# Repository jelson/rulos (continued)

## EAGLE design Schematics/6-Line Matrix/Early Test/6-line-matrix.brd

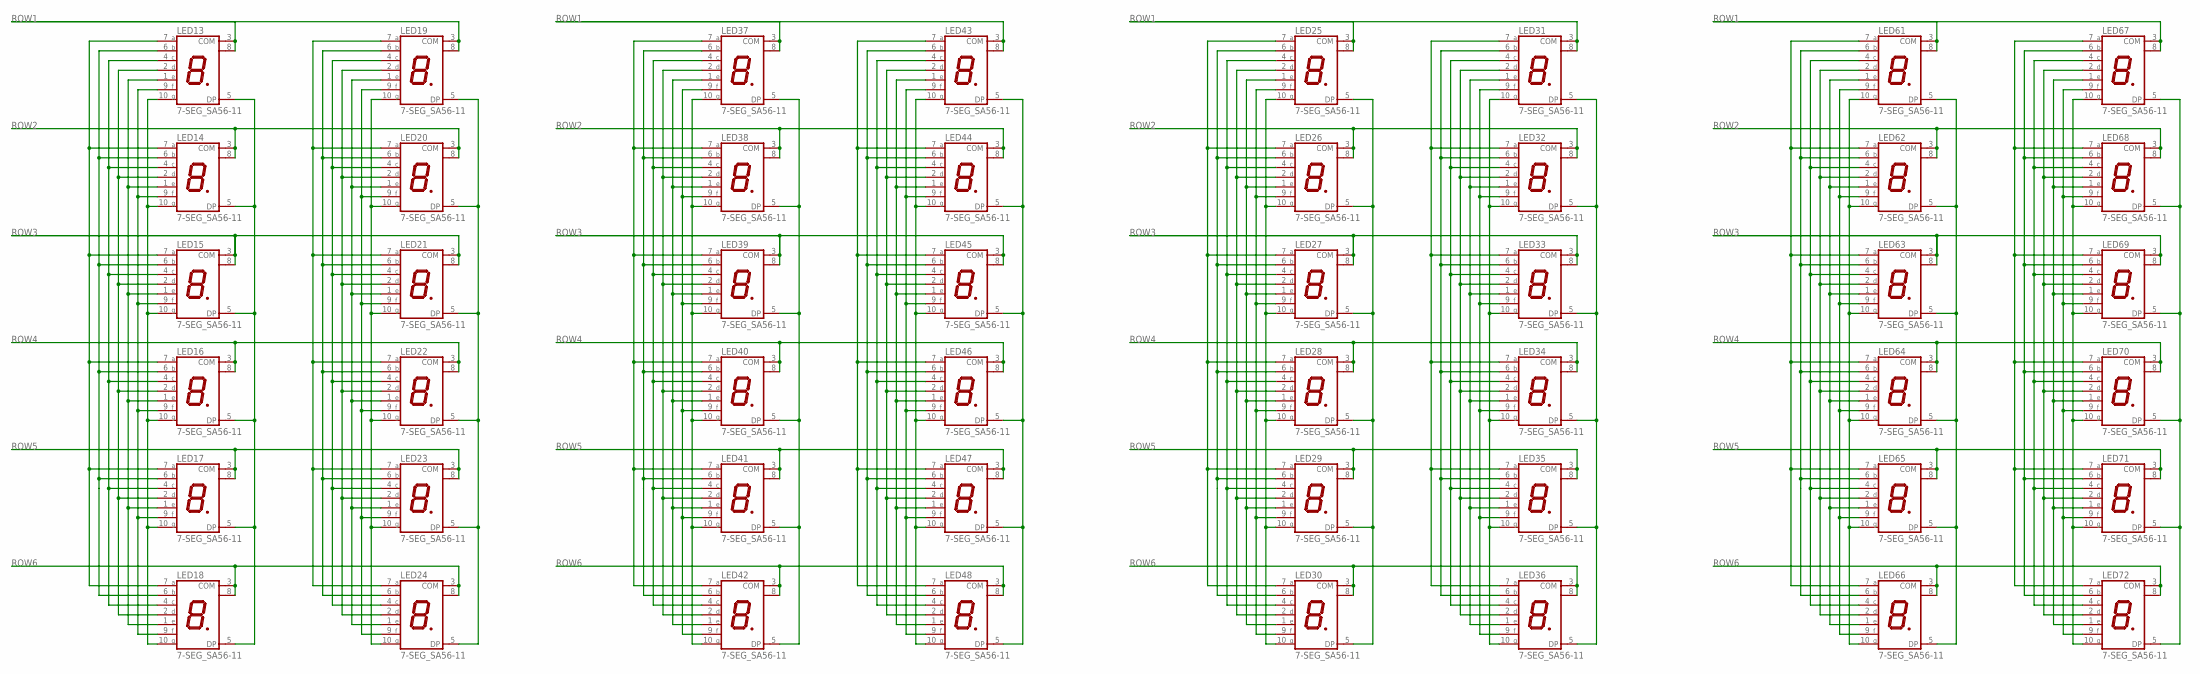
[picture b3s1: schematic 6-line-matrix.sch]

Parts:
LED13, LED14, LED15, LED16, LED17, LED18, LED19, LED20, LED21, LED22, LED23, LED24, LED25, LED26, LED27, LED28, LED29, LED30, LED31, LED32, LED33, LED34, LED35, LED36, LED37, LED38, LED39, LED40, LED41, LED42, LED43, LED44, LED45, LED46, LED47, LED48, LED61, LED62, LED63, LED64, LED65, LED66, LED67, LED68, LED69, LED70, LED71, LED72: 7-SEG_SA56-11; SA56-11

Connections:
unnamed: LED13.7 (A), LED14.7 (A), LED15.7 (A), LED16.7 (A), LED17.7 (A), LED18.7 (A)
unnamed: LED13.6 (B), LED14.6 (B), LED15.6 (B), LED16.6 (B), LED17.6 (B), LED18.6 (B)
unnamed: LED13.10 (G), LED14.10 (G), LED15.10 (G), LED16.10 (G), LED17.10 (G), LED18.10 (G)
unnamed: LED13.9 (F), LED14.9 (F), LED15.9 (F), LED16.9 (F), LED17.9 (F), LED18.9 (F)
unnamed: LED13.1 (E), LED14.1 (E), LED15.1 (E), LED16.1 (E), LED17.1 (E), LED18.1 (E)
unnamed: LED13.2 (D), LED14.2 (D), LED15.2 (D), LED16.2 (D), LED17.2 (D), LED18.2 (D)
unnamed: LED13.4 (C), LED14.4 (C), LED15.4 (C), LED16.4 (C), LED17.4 (C), LED18.4 (C)
unnamed: LED13.5 (DP), LED14.5 (DP), LED15.5 (DP), LED16.5 (DP), LED17.5 (DP), LED18.5 (DP)
unnamed: LED19.10 (G), LED20.10 (G), LED21.10 (G), LED22.10 (G), LED23.10 (G), LED24.10 (G)
unnamed: LED19.9 (F), LED20.9 (F), LED21.9 (F), LED22.9 (F), LED23.9 (F), LED24.9 (F)
unnamed: LED19.1 (E), LED20.1 (E), LED21.1 (E), LED22.1 (E), LED23.1 (E), LED24.1 (E)
unnamed: LED19.2 (D), LED20.2 (D), LED21.2 (D), LED22.2 (D), LED23.2 (D), LED24.2 (D)
unnamed: LED19.4 (C), LED20.4 (C), LED21.4 (C), LED22.4 (C), LED23.4 (C), LED24.4 (C)
unnamed: LED19.6 (B), LED20.6 (B), LED21.6 (B), LED22.6 (B), LED23.6 (B), LED24.6 (B)
unnamed: LED19.7 (A), LED20.7 (A), LED21.7 (A), LED22.7 (A), LED23.7 (A), LED24.7 (A)
unnamed: LED19.5 (DP), LED20.5 (DP), LED21.5 (DP), LED22.5 (DP), LED23.5 (DP), LED24.5 (DP)
unnamed: LED25.7 (A), LED26.7 (A), LED27.7 (A), LED28.7 (A), LED29.7 (A), LED30.7 (A)
unnamed: LED25.6 (B), LED26.6 (B), LED27.6 (B), LED28.6 (B), LED29.6 (B), LED30.6 (B)
unnamed: LED25.10 (G), LED26.10 (G), LED27.10 (G), LED28.10 (G), LED29.10 (G), LED30.10 (G)
unnamed: LED25.9 (F), LED26.9 (F), LED27.9 (F), LED28.9 (F), LED29.9 (F), LED30.9 (F)
unnamed: LED25.1 (E), LED26.1 (E), LED27.1 (E), LED28.1 (E), LED29.1 (E), LED30.1 (E)
unnamed: LED25.2 (D), LED26.2 (D), LED27.2 (D), LED28.2 (D), LED29.2 (D), LED30.2 (D)
unnamed: LED25.4 (C), LED26.4 (C), LED27.4 (C), LED28.4 (C), LED29.4 (C), LED30.4 (C)
unnamed: LED25.5 (DP), LED26.5 (DP), LED27.5 (DP), LED28.5 (DP), LED29.5 (DP), LED30.5 (DP)
unnamed: LED31.10 (G), LED32.10 (G), LED33.10 (G), LED34.10 (G), LED35.10 (G), LED36.10 (G)
unnamed: LED31.9 (F), LED32.9 (F), LED33.9 (F), LED34.9 (F), LED35.9 (F), LED36.9 (F)
unnamed: LED31.1 (E), LED32.1 (E), LED33.1 (E), LED34.1 (E), LED35.1 (E), LED36.1 (E)
unnamed: LED31.2 (D), LED32.2 (D), LED33.2 (D), LED34.2 (D), LED35.2 (D), LED36.2 (D)
unnamed: LED31.4 (C), LED32.4 (C), LED33.4 (C), LED34.4 (C), LED35.4 (C), LED36.4 (C)
unnamed: LED31.6 (B), LED32.6 (B), LED33.6 (B), LED34.6 (B), LED35.6 (B), LED36.6 (B)
unnamed: LED31.7 (A), LED32.7 (A), LED33.7 (A), LED34.7 (A), LED35.7 (A), LED36.7 (A)
unnamed: LED31.5 (DP), LED32.5 (DP), LED33.5 (DP), LED34.5 (DP), LED35.5 (DP), LED36.5 (DP)
unnamed: LED37.7 (A), LED38.7 (A), LED39.7 (A), LED40.7 (A), LED41.7 (A), LED42.7 (A)
unnamed: LED37.6 (B), LED38.6 (B), LED39.6 (B), LED40.6 (B), LED41.6 (B), LED42.6 (B)
unnamed: LED37.10 (G), LED38.10 (G), LED39.10 (G), LED40.10 (G), LED41.10 (G), LED42.10 (G)
unnamed: LED37.9 (F), LED38.9 (F), LED39.9 (F), LED40.9 (F), LED41.9 (F), LED42.9 (F)
unnamed: LED37.1 (E), LED38.1 (E), LED39.1 (E), LED40.1 (E), LED41.1 (E), LED42.1 (E)
unnamed: LED37.2 (D), LED38.2 (D), LED39.2 (D), LED40.2 (D), LED41.2 (D), LED42.2 (D)
unnamed: LED37.4 (C), LED38.4 (C), LED39.4 (C), LED40.4 (C), LED41.4 (C), LED42.4 (C)
unnamed: LED37.5 (DP), LED38.5 (DP), LED39.5 (DP), LED40.5 (DP), LED41.5 (DP), LED42.5 (DP)
unnamed: LED43.10 (G), LED44.10 (G), LED45.10 (G), LED46.10 (G), LED47.10 (G), LED48.10 (G)
unnamed: LED43.9 (F), LED44.9 (F), LED45.9 (F), LED46.9 (F), LED47.9 (F), LED48.9 (F)
unnamed: LED43.1 (E), LED44.1 (E), LED45.1 (E), LED46.1 (E), LED47.1 (E), LED48.1 (E)
unnamed: LED43.2 (D), LED44.2 (D), LED45.2 (D), LED46.2 (D), LED47.2 (D), LED48.2 (D)
unnamed: LED43.4 (C), LED44.4 (C), LED45.4 (C), LED46.4 (C), LED47.4 (C), LED48.4 (C)
unnamed: LED43.6 (B), LED44.6 (B), LED45.6 (B), LED46.6 (B), LED47.6 (B), LED48.6 (B)
unnamed: LED43.7 (A), LED44.7 (A), LED45.7 (A), LED46.7 (A), LED47.7 (A), LED48.7 (A)
unnamed: LED43.5 (DP), LED44.5 (DP), LED45.5 (DP), LED46.5 (DP), LED47.5 (DP), LED48.5 (DP)
unnamed: LED61.7 (A), LED62.7 (A), LED63.7 (A), LED64.7 (A), LED65.7 (A), LED66.7 (A)
unnamed: LED61.6 (B), LED62.6 (B), LED63.6 (B), LED64.6 (B), LED65.6 (B), LED66.6 (B)
unnamed: LED61.10 (G), LED62.10 (G), LED63.10 (G), LED64.10 (G), LED65.10 (G), LED66.10 (G)
unnamed: LED61.9 (F), LED62.9 (F), LED63.9 (F), LED64.9 (F), LED65.9 (F), LED66.9 (F)
unnamed: LED61.1 (E), LED62.1 (E), LED63.1 (E), LED64.1 (E), LED65.1 (E), LED66.1 (E)
unnamed: LED61.2 (D), LED62.2 (D), LED63.2 (D), LED64.2 (D), LED65.2 (D), LED66.2 (D)
unnamed: LED61.4 (C), LED62.4 (C), LED63.4 (C), LED64.4 (C), LED65.4 (C), LED66.4 (C)
unnamed: LED61.5 (DP), LED62.5 (DP), LED63.5 (DP), LED64.5 (DP), LED65.5 (DP), LED66.5 (DP)
unnamed: LED67.10 (G), LED68.10 (G), LED69.10 (G), LED70.10 (G), LED71.10 (G), LED72.10 (G)
unnamed: LED67.9 (F), LED68.9 (F), LED69.9 (F), LED70.9 (F), LED71.9 (F), LED72.9 (F)
unnamed: LED67.1 (E), LED68.1 (E), LED69.1 (E), LED70.1 (E), LED71.1 (E), LED72.1 (E)
unnamed: LED67.2 (D), LED68.2 (D), LED69.2 (D), LED70.2 (D), LED71.2 (D), LED72.2 (D)
unnamed: LED67.4 (C), LED68.4 (C), LED69.4 (C), LED70.4 (C), LED71.4 (C), LED72.4 (C)
unnamed: LED67.6 (B), LED68.6 (B), LED69.6 (B), LED70.6 (B), LED71.6 (B), LED72.6 (B)
unnamed: LED67.7 (A), LED68.7 (A), LED69.7 (A), LED70.7 (A), LED71.7 (A), LED72.7 (A)
unnamed: LED67.5 (DP), LED68.5 (DP), LED69.5 (DP), LED70.5 (DP), LED71.5 (DP), LED72.5 (DP)
ROW1: LED13.3 (COM), LED13.8 (COM), LED19.3 (COM), LED19.8 (COM), LED25.3 (COM), LED25.8 (COM), LED31.3 (COM), LED31.8 (COM), LED37.3 (COM), LED37.8 (COM), LED43.3 (COM), LED43.8 (COM), LED61.3 (COM), LED61.8 (COM), LED67.3 (COM), LED67.8 (COM)
ROW2: LED14.3 (COM), LED14.8 (COM), LED20.3 (COM), LED20.8 (COM), LED26.3 (COM), LED26.8 (COM), LED32.3 (COM), LED32.8 (COM), LED38.3 (COM), LED38.8 (COM), LED44.3 (COM), LED44.8 (COM), LED62.3 (COM), LED62.8 (COM), LED68.3 (COM), LED68.8 (COM)
ROW3: LED15.3 (COM), LED15.8 (COM), LED21.3 (COM), LED21.8 (COM), LED27.3 (COM), LED27.8 (COM), LED33.3 (COM), LED33.8 (COM), LED39.3 (COM), LED39.8 (COM), LED45.3 (COM), LED45.8 (COM), LED63.3 (COM), LED63.8 (COM), LED69.3 (COM), LED69.8 (COM)
ROW4: LED16.3 (COM), LED16.8 (COM), LED22.3 (COM), LED22.8 (COM), LED28.3 (COM), LED28.8 (COM), LED34.3 (COM), LED34.8 (COM), LED40.3 (COM), LED40.8 (COM), LED46.3 (COM), LED46.8 (COM), LED64.3 (COM), LED64.8 (COM), LED70.3 (COM), LED70.8 (COM)
ROW5: LED17.3 (COM), LED17.8 (COM), LED23.3 (COM), LED23.8 (COM), LED29.3 (COM), LED29.8 (COM), LED35.3 (COM), LED35.8 (COM), LED41.3 (COM), LED41.8 (COM), LED47.3 (COM), LED47.8 (COM), LED65.3 (COM), LED65.8 (COM), LED71.3 (COM), LED71.8 (COM)
ROW6: LED18.3 (COM), LED18.8 (COM), LED24.3 (COM), LED24.8 (COM), LED30.3 (COM), LED30.8 (COM), LED36.3 (COM), LED36.8 (COM), LED42.3 (COM), LED42.8 (COM), LED48.3 (COM), LED48.8 (COM), LED66.3 (COM), LED66.8 (COM), LED72.3 (COM), LED72.8 (COM)

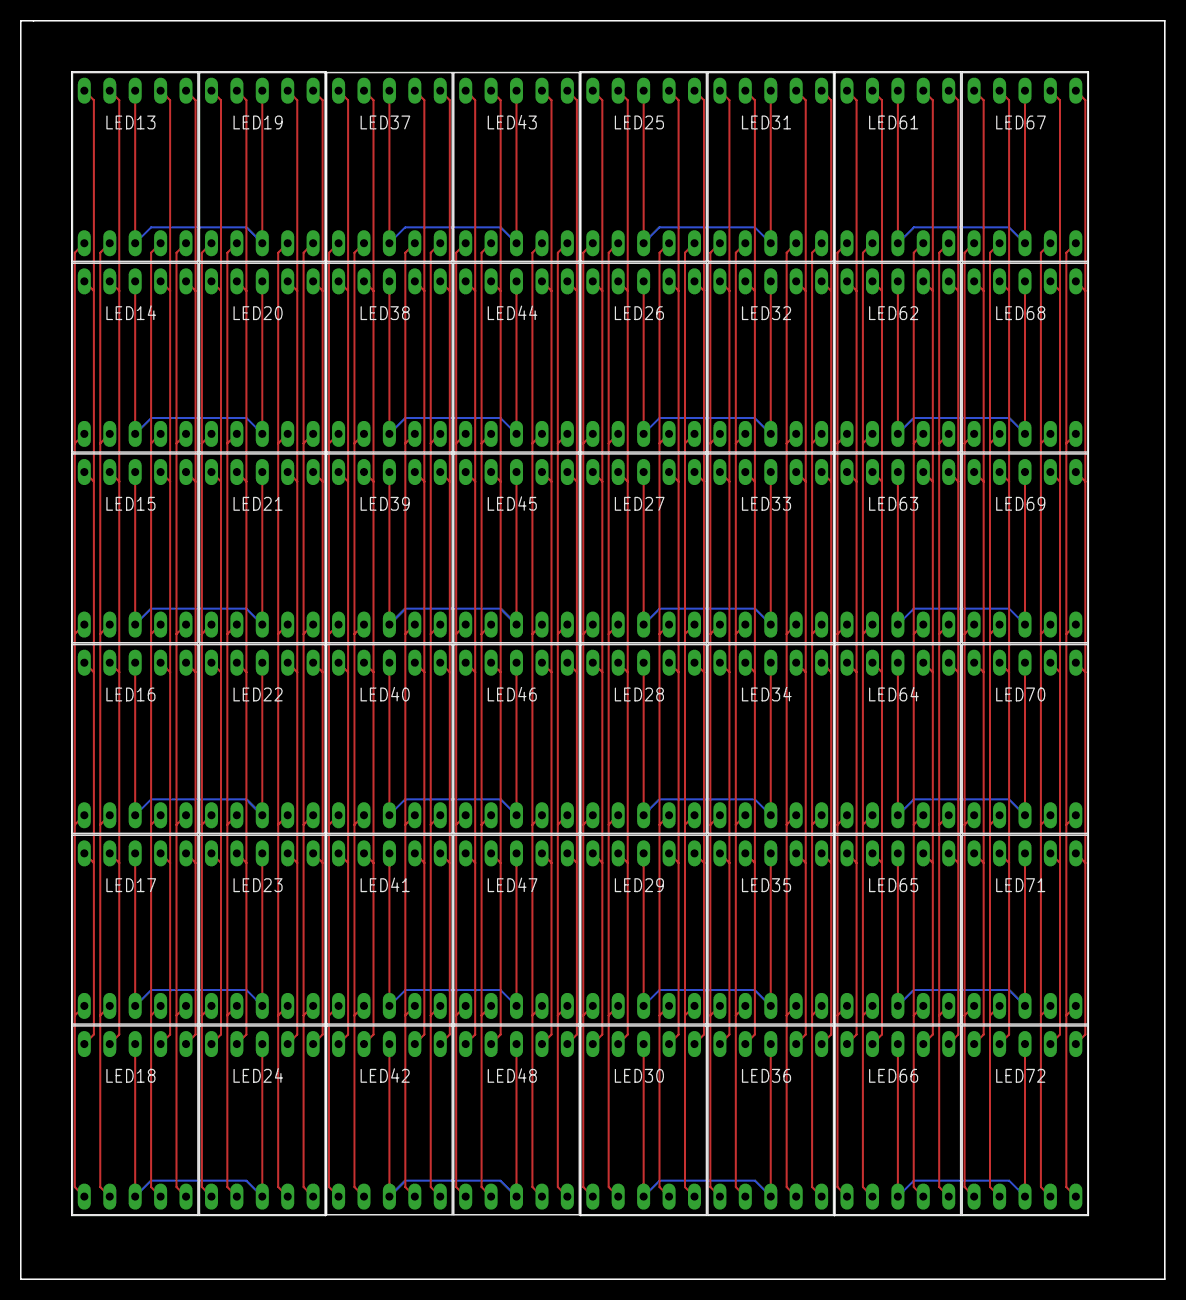
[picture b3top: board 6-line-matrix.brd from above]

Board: 2 copper layers, 114.3 x 125.7 mm, 48 parts (0 on the bottom side), 70 nets.

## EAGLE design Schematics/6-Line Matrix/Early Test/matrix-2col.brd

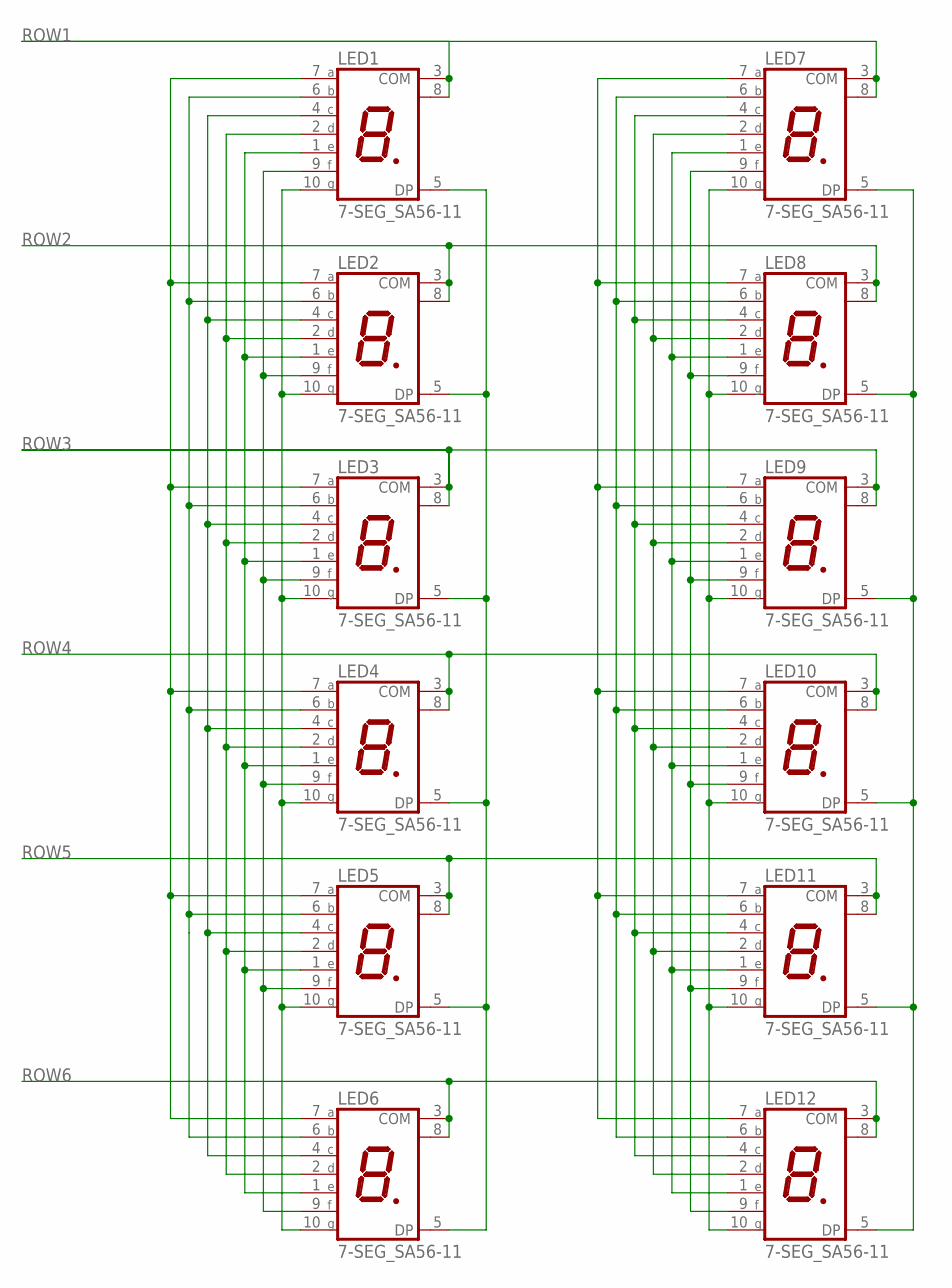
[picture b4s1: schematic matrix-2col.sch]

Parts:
LED1, LED2, LED3, LED4, LED5, LED6, LED7, LED8, LED9, LED10, LED11, LED12: 7-SEG_SA56-11; SA56-11

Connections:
unnamed: LED1.10 (G), LED2.10 (G), LED3.10 (G), LED4.10 (G), LED5.10 (G), LED6.10 (G)
unnamed: LED1.5 (DP), LED2.5 (DP), LED3.5 (DP), LED4.5 (DP), LED5.5 (DP), LED6.5 (DP)
unnamed: LED7.10 (G), LED8.10 (G), LED9.10 (G), LED10.10 (G), LED11.10 (G), LED12.10 (G)
unnamed: LED7.9 (F), LED8.9 (F), LED9.9 (F), LED10.9 (F), LED11.9 (F), LED12.9 (F)
unnamed: LED7.1 (E), LED8.1 (E), LED9.1 (E), LED10.1 (E), LED11.1 (E), LED12.1 (E)
unnamed: LED1.7 (A), LED2.7 (A), LED3.7 (A), LED4.7 (A), LED5.7 (A), LED6.7 (A)
unnamed: LED1.6 (B), LED2.6 (B), LED3.6 (B), LED4.6 (B), LED5.6 (B), LED6.6 (B)
unnamed: LED1.9 (F), LED2.9 (F), LED3.9 (F), LED4.9 (F), LED5.9 (F), LED6.9 (F)
unnamed: LED1.1 (E), LED2.1 (E), LED3.1 (E), LED4.1 (E), LED5.1 (E), LED6.1 (E)
unnamed: LED1.2 (D), LED2.2 (D), LED3.2 (D), LED4.2 (D), LED5.2 (D), LED6.2 (D)
unnamed: LED1.4 (C), LED2.4 (C), LED3.4 (C), LED4.4 (C), LED5.4 (C), LED6.4 (C)
unnamed: LED7.2 (D), LED8.2 (D), LED9.2 (D), LED10.2 (D), LED11.2 (D), LED12.2 (D)
unnamed: LED7.4 (C), LED8.4 (C), LED9.4 (C), LED10.4 (C), LED11.4 (C), LED12.4 (C)
unnamed: LED7.6 (B), LED8.6 (B), LED9.6 (B), LED10.6 (B), LED11.6 (B), LED12.6 (B)
unnamed: LED7.7 (A), LED8.7 (A), LED9.7 (A), LED10.7 (A), LED11.7 (A), LED12.7 (A)
unnamed: LED7.5 (DP), LED8.5 (DP), LED9.5 (DP), LED10.5 (DP), LED11.5 (DP), LED12.5 (DP)
ROW1: LED1.3 (COM), LED1.8 (COM), LED7.3 (COM), LED7.8 (COM)
ROW2: LED2.3 (COM), LED2.8 (COM), LED8.3 (COM), LED8.8 (COM)
ROW3: LED3.3 (COM), LED3.8 (COM), LED9.3 (COM), LED9.8 (COM)
ROW4: LED4.3 (COM), LED4.8 (COM), LED10.3 (COM), LED10.8 (COM)
ROW5: LED5.3 (COM), LED5.8 (COM), LED11.3 (COM), LED11.8 (COM)
ROW6: LED6.3 (COM), LED6.8 (COM), LED12.3 (COM), LED12.8 (COM)

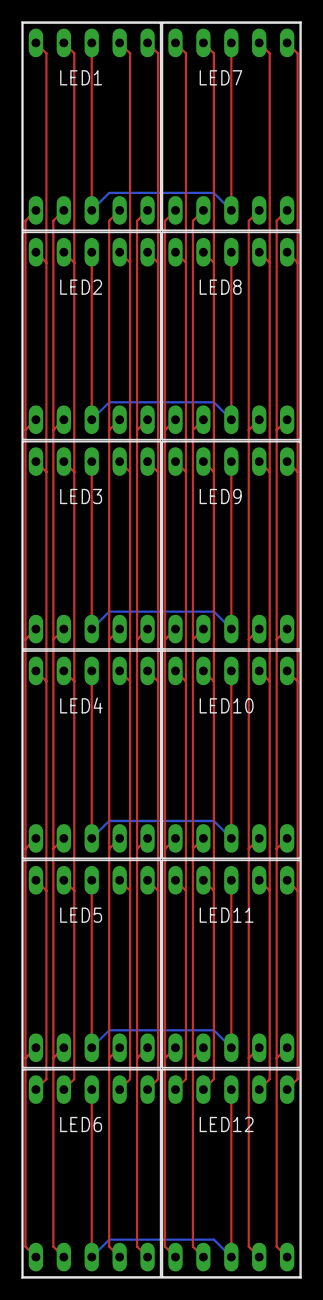
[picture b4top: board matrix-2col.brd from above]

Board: 2 copper layers, 25.4 x 114.3 mm, 12 parts (0 on the bottom side), 22 nets.

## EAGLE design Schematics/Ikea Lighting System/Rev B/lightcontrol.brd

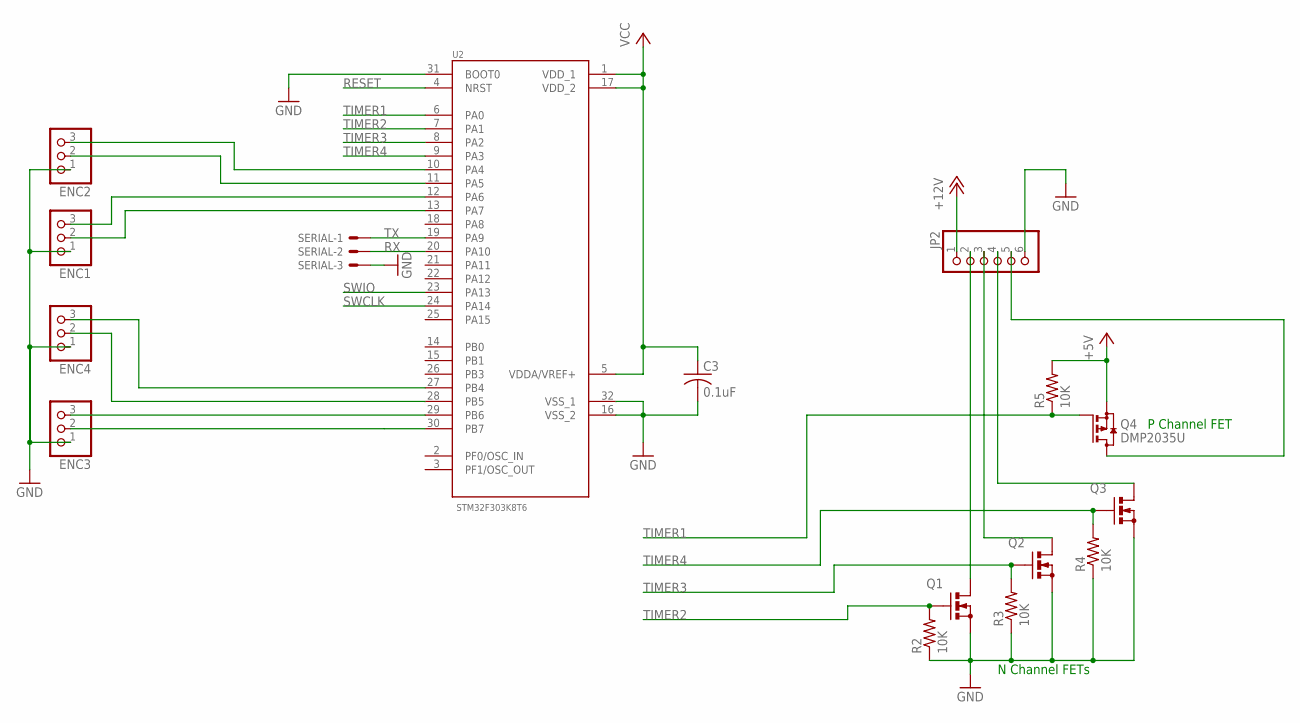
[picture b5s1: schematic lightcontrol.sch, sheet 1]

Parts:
C3: 0.1uF; C0603
ENC1, ENC2, ENC3, ENC4: PINHD-1X3; 1X03
JP2: PINHD-1X6/90; 1X06/90
Q1, Q2, Q3: BS170; SOT54E
Q4: DMP2035U; SOT23
R2, R3, R4, R5: 10K; 0204/5
SERIAL: 22-23-2031
U2: STM32F303K8T6; QFP80P900X900X160-32N

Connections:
+5V: Q4.2 (S), R5.2; also elsewhere on the board
+12V: JP2.1; also elsewhere on the board
GND: C3.2, ENC1.1, ENC2.1, ENC3.1, ENC4.1, JP2.6, Q1.S, Q2.S, Q3.S, R2.1, R3.1, R4.1, SERIAL.3, U2.16 (VSS_2), U2.31 (BOOT0), U2.32 (VSS_1); also elsewhere on the board
unnamed: ENC3.2, U2.30 (PB7)
unnamed: ENC2.3, U2.10 (PA4)
unnamed: ENC3.3, U2.29 (PB6)
unnamed: ENC4.2, U2.28 (PB5)
unnamed: JP2.2, Q1.D
unnamed: ENC2.2, U2.11 (PA5)
unnamed: JP2.3, Q2.D
unnamed: ENC4.3, U2.27 (PB4)
unnamed: JP2.4, Q3.D
unnamed: JP2.5, Q4.3 (D)
unnamed: ENC1.3, U2.12 (PA6)
unnamed: ENC1.2, U2.13 (PA7)
RESET: U2.4 (NRST); also elsewhere on the board
RX: SERIAL.2, U2.20 (PA10)
SWCLK: U2.24 (PA14); also elsewhere on the board
SWIO: U2.23 (PA13); also elsewhere on the board
TIMER1: Q4.1 (G), R5.1, U2.6 (PA0)
TIMER2: Q1.G, R2.2, U2.7 (PA1)
TIMER3: Q2.G, R3.2, U2.8 (PA2)
TIMER4: Q3.G, R4.2, U2.9 (PA3)
TX: SERIAL.1, U2.19 (PA9)
VCC: C3.1, U2.1 (VDD_1), U2.5 (VDDA/VREF+), U2.17 (VDD_2); also elsewhere on the board

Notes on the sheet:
N Channel FETs
P Channel FET

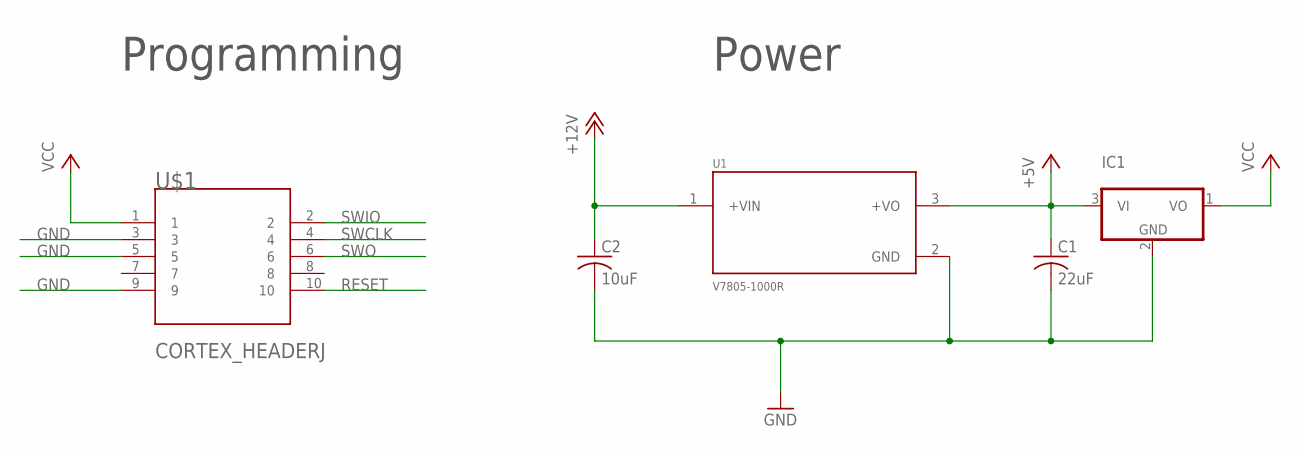
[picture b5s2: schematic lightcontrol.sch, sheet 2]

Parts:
C1: 22uF; C050-035X075
C2: 10uF; C050-035X075
IC1: 7803; TO92
U1: V7805-1000R; CONV_V7805-1000R
U$1: CORTEX_HEADERJ; CORTEX_HEADER

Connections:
+5V: C1.1, IC1.3 (VI), U1.3 (+VO); also elsewhere on the board
+12V: C2.1, U1.1 (+VIN); also elsewhere on the board
GND: C1.2, C2.2, IC1.2 (GND), U1.2 (GND), U$1.3, U$1.5, U$1.9; also elsewhere on the board
RESET: U$1.10; also elsewhere on the board
SWCLK: U$1.4; also elsewhere on the board
SWIO: U$1.2; also elsewhere on the board
SWO: U$1.6
VCC: IC1.1 (VO), U$1.1; also elsewhere on the board

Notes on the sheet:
Programming
Power

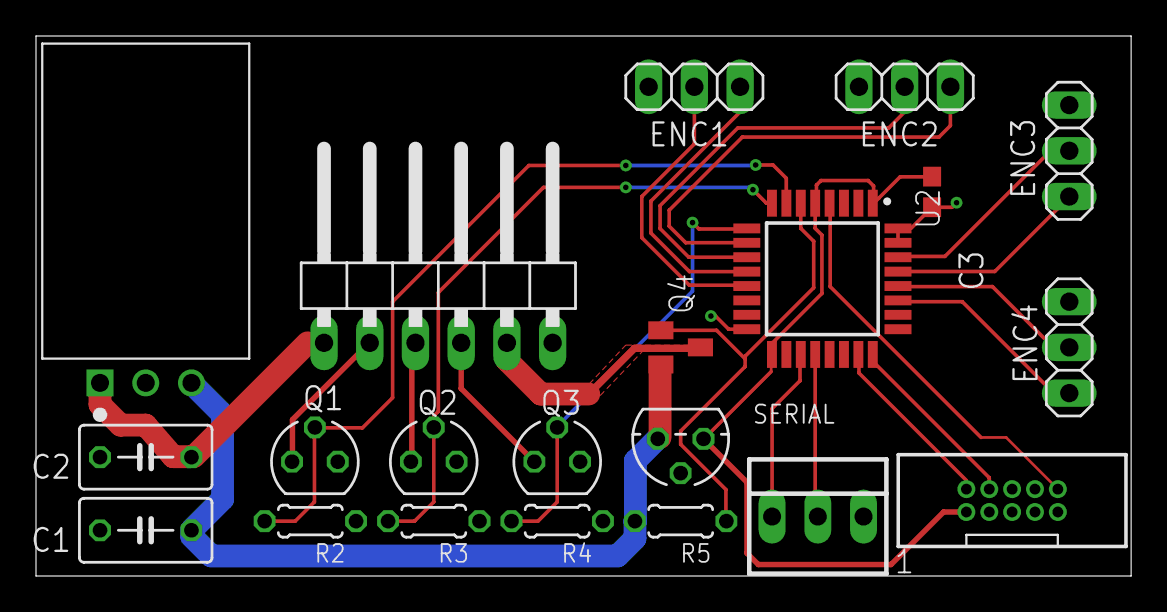
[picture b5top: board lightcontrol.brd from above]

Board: 2 copper layers, 60.8 x 30.0 mm, 21 parts (0 on the bottom side), 25 nets.

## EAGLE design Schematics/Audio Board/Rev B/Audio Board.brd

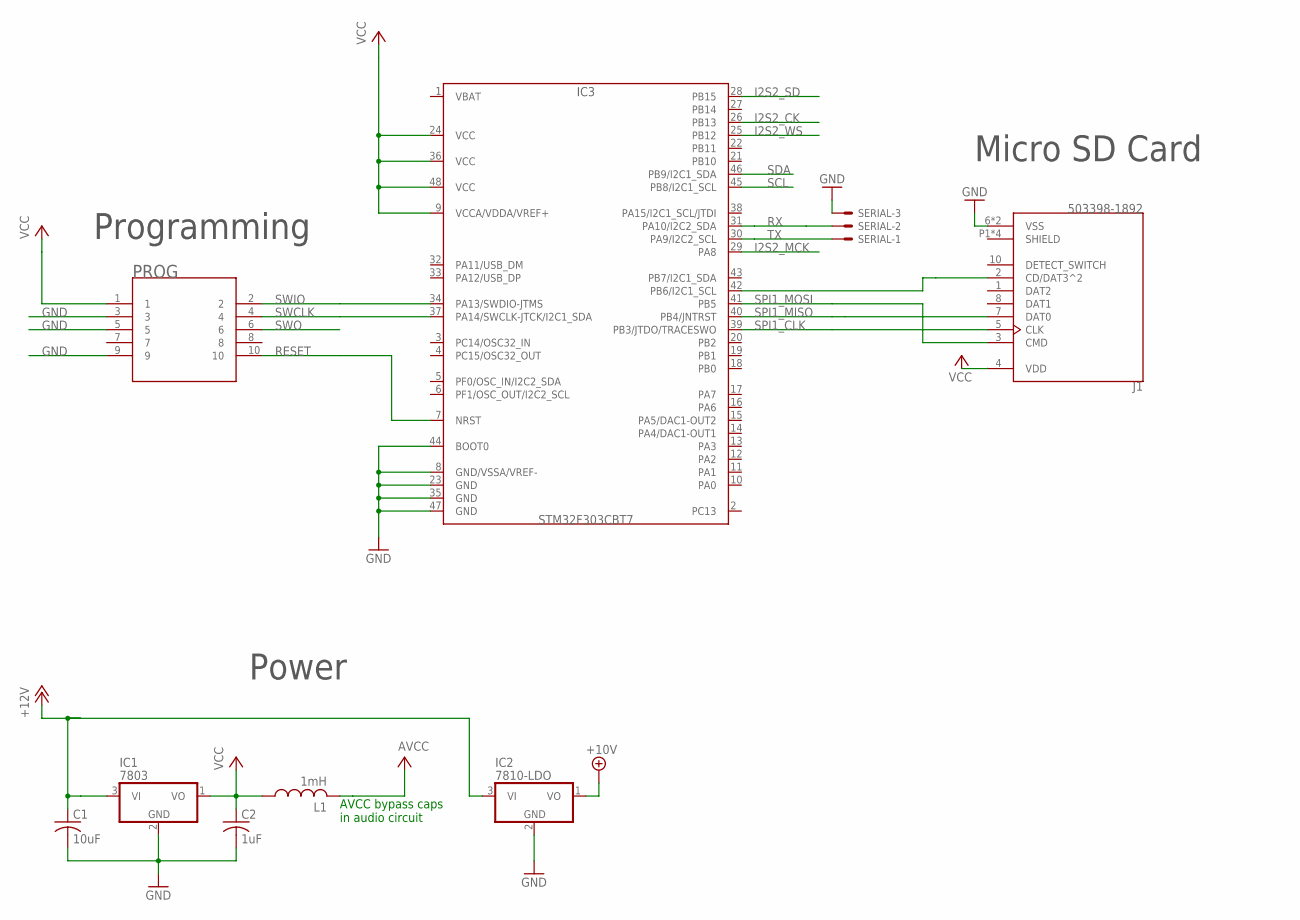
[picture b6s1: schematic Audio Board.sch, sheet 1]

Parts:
C1: 10uF; C025-025X050
C2: 1uF; C025-025X050
IC1: 7803; TO92
IC2: 7810-LDO; TO92
IC3: STM32F303CBT7; LQFP48
J1: 503398-1892; MOLEX_503398-1892
L1: 1mH; 0207/10
PROG: CORTEX_HEADERJ; CORTEX_HEADER
SERIAL: 22-23-2031

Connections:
+10V: IC2.1 (VO); also elsewhere on the board
+12V: C1.1, IC1.3 (VI), IC2.3 (VI); also elsewhere on the board
GND: C1.2, C2.2, IC1.2 (GND), IC2.2 (GND), IC3.8 (GND/VSSA/VREF-), IC3.23 (GND), IC3.35 (GND), IC3.44 (BOOT0), IC3.47 (GND), J1.6 (VSS), J1.9 (VSS), PROG.3, PROG.5, PROG.9, SERIAL.3; also elsewhere on the board
I2S2_CK: IC3.26 (PB13); also elsewhere on the board
I2S2_MCK: IC3.29 (PA8); also elsewhere on the board
I2S2_SD: IC3.28 (PB15); also elsewhere on the board
I2S2_WS: IC3.25 (PB12); also elsewhere on the board
unnamed: IC3.42 (PB6/I2C1_SCL), J1.2 (CD/DAT3^2)
RESET: IC3.7 (NRST), PROG.10
RX: IC3.31 (PA10/I2C2_SDA), SERIAL.2
SCL: IC3.45 (PB8/I2C1_SCL); also elsewhere on the board
SDA: IC3.46 (PB9/I2C1_SDA); also elsewhere on the board
SPI1_CLK: IC3.39 (PB3/JTDO/TRACESWO), J1.5 (CLK)
SPI1_MISO: IC3.40 (PB4/JNTRST), J1.7 (DAT0)
SPI1_MOSI: IC3.41 (PB5), J1.3 (CMD)
SWCLK: IC3.37 (PA14/SWCLK-JTCK/I2C1_SDA), PROG.4
SWIO: IC3.34 (PA13/SWDIO-JTMS), PROG.2
SWO: PROG.6
TX: IC3.30 (PA9/I2C2_SCL), SERIAL.1
V+: L1.2; also elsewhere on the board
VCC: C2.1, IC1.1 (VO), IC3.9 (VCCA/VDDA/VREF+), IC3.24 (VCC), IC3.36 (VCC), IC3.48 (VCC), J1.4 (VDD), L1.1, PROG.1; also elsewhere on the board

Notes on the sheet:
Programming
Power
Micro SD Card
AVCC bypass caps in audio circuit

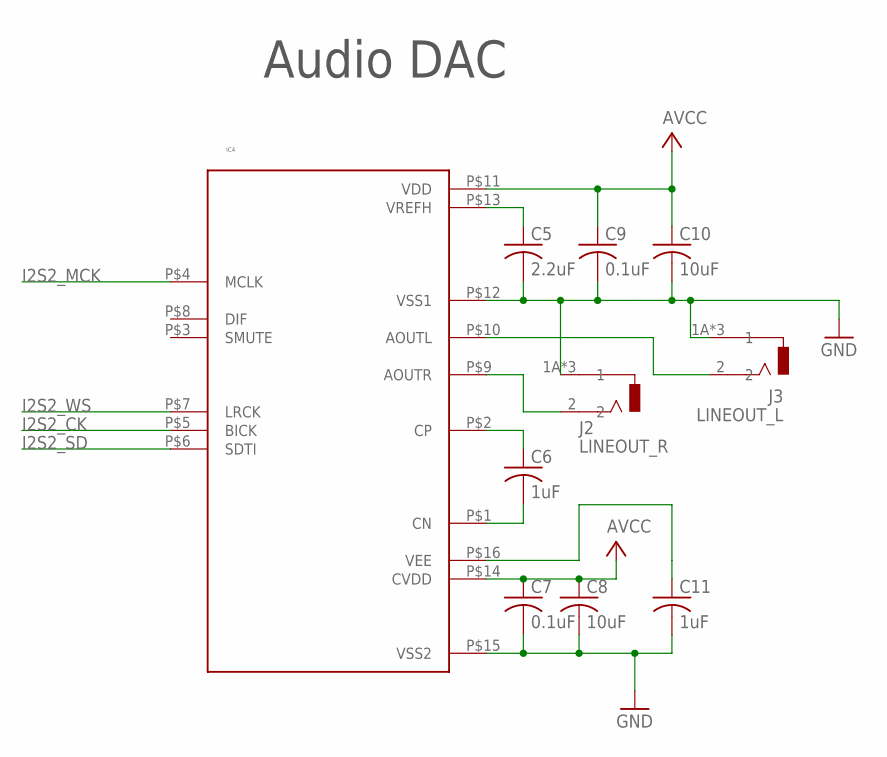
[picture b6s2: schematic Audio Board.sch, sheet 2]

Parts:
C5: 2.2uF; C025-025X050
C6, C11: 1uF; C025-025X050
C7, C9: 0.1uF; C025-025X050
C8, C10: 10uF; C025-025X050
IC4: AK4430ET; 16TSSOP
J2: LINEOUT_R; CUI_RCJ-012
J3: LINEOUT_L; CUI_RCJ-012

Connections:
GND: C5.2, C7.2, C8.2, C9.2, C10.2, C11.2, IC4.P$12 (VSS1), IC4.P$15 (VSS2), J2.1A (1), J2.1B (1), J2.1C (1), J3.1A (1), J3.1B (1), J3.1C (1); also elsewhere on the board
GND1: C6.2, IC4.P$1 (CN)
I2S2_CK: IC4.P$5 (BICK); also elsewhere on the board
I2S2_MCK: IC4.P$4 (MCLK); also elsewhere on the board
I2S2_SD: IC4.P$6 (SDTI); also elsewhere on the board
I2S2_WS: IC4.P$7 (LRCK); also elsewhere on the board
unnamed: C11.1, IC4.P$16 (VEE)
unnamed: IC4.P$10 (AOUTL), J3.2
unnamed: IC4.P$9 (AOUTR), J2.2
unnamed: C5.1, IC4.P$13 (VREFH)
V+: C7.1, C8.1, C9.1, C10.1, IC4.P$11 (VDD), IC4.P$14 (CVDD); also elsewhere on the board
V+1: C6.1, IC4.P$2 (CP)

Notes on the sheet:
Audio DAC

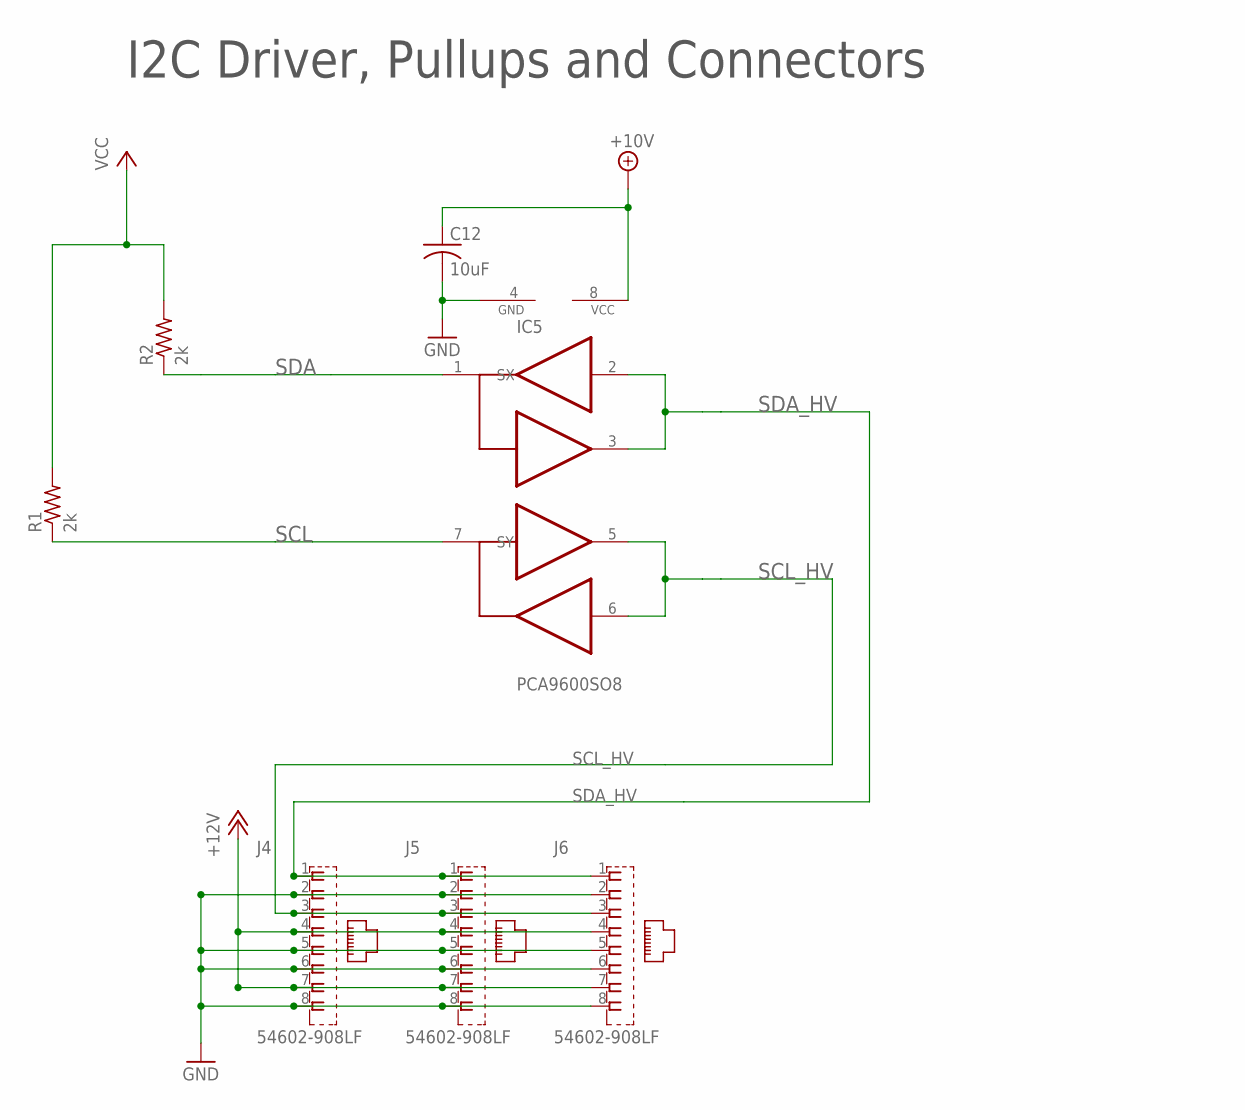
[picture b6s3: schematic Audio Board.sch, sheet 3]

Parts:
C12: 10uF; C025-025X050
IC5: PCA9600SO8; SO08
J4, J5, J6: 54602-908LF; AMPHENOL_54602-908LF
R1, R2: 2k; 0204/5

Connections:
+10V: C12.1, IC5.8 (VCC); also elsewhere on the board
+12V: J4.4, J4.7, J5.4, J5.7, J6.4, J6.7; also elsewhere on the board
GND: C12.2, IC5.4 (GND), J4.2, J4.5, J4.6, J4.8, J5.2, J5.5, J5.6, J5.8, J6.2, J6.5, J6.6, J6.8; also elsewhere on the board
SCL: IC5.7 (SY), R1.1; also elsewhere on the board
SCL_HV: IC5.5 (TY), IC5.6 (RY), J4.3, J5.3, J6.3
SDA: IC5.1 (SX), R2.1; also elsewhere on the board
SDA_HV: IC5.2 (RX), IC5.3 (TX), J4.1, J5.1, J6.1
VCC: R1.2, R2.2; also elsewhere on the board

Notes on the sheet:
I2C Driver, Pullups and Connectors

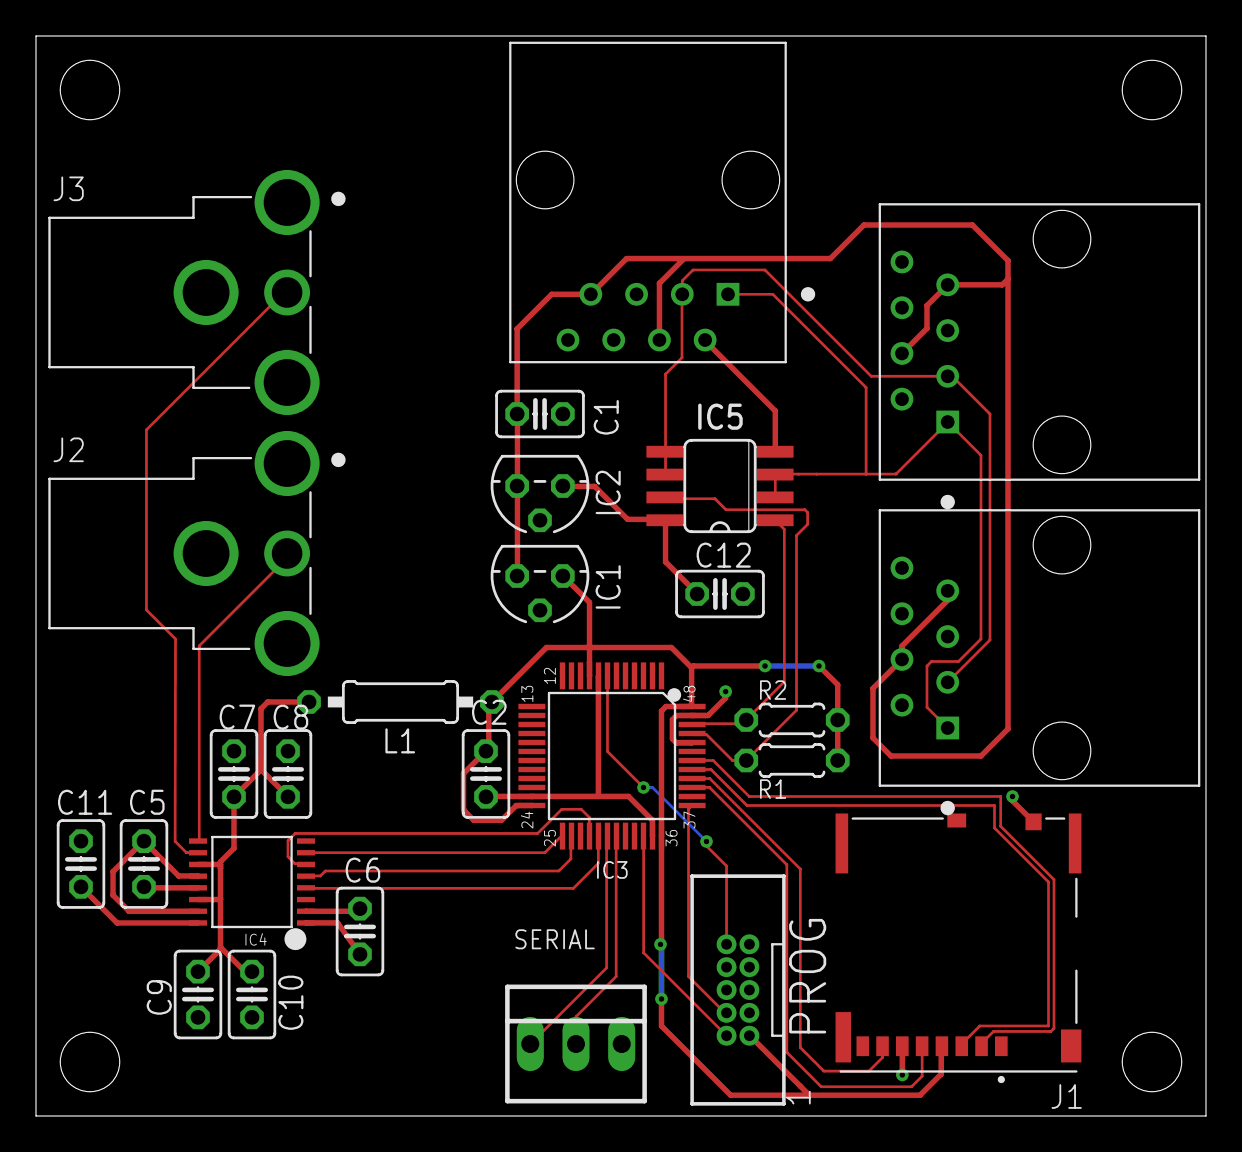
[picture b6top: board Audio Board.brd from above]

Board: 2 copper layers, 65.0 x 60.0 mm, 30 parts (0 on the bottom side), 28 nets.

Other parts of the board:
U$1, U$2, U$3, U$4: STAND-OFF
